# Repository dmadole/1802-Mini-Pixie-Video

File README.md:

# 1802-Mini-Pixie-Video
This is the Pixie video card for the [1802/Mini](https://github.com/dmadole/1802-Mini) system. It supports the following features:

* Software compatible with CDP1861 Pixie chip
* Composite video output with improved sync signalling
* Uses WAIT to syncronize to processor rather than losing sync
* Processor runs at full speed when video is diabled
* Optionally runs processor at full speed outside display area
* Outputs video levels for 75-ohm or high-impedance inputs
* Requires no programmable components, only common 4000-series CMOS
* Supports group I/O port expansion
* Fixed port address of 1 compatible with VIP and Studio II
* Jumper-selected display field polling bit on EF1-EF4

Gerber files for the PCBs and PDF schematics can be found in [Releases](https://github.com/dmadole/1802-Mini-Pixie-Video/releases).

BOMS and any applicable errata or other notes can be found in [notes](https://github.com/dmadole/1802-Mini-Pixie-Video/tree/main/notes).

For availability of kits and bare PCBs please see http://madole.net/1802/mini/kits

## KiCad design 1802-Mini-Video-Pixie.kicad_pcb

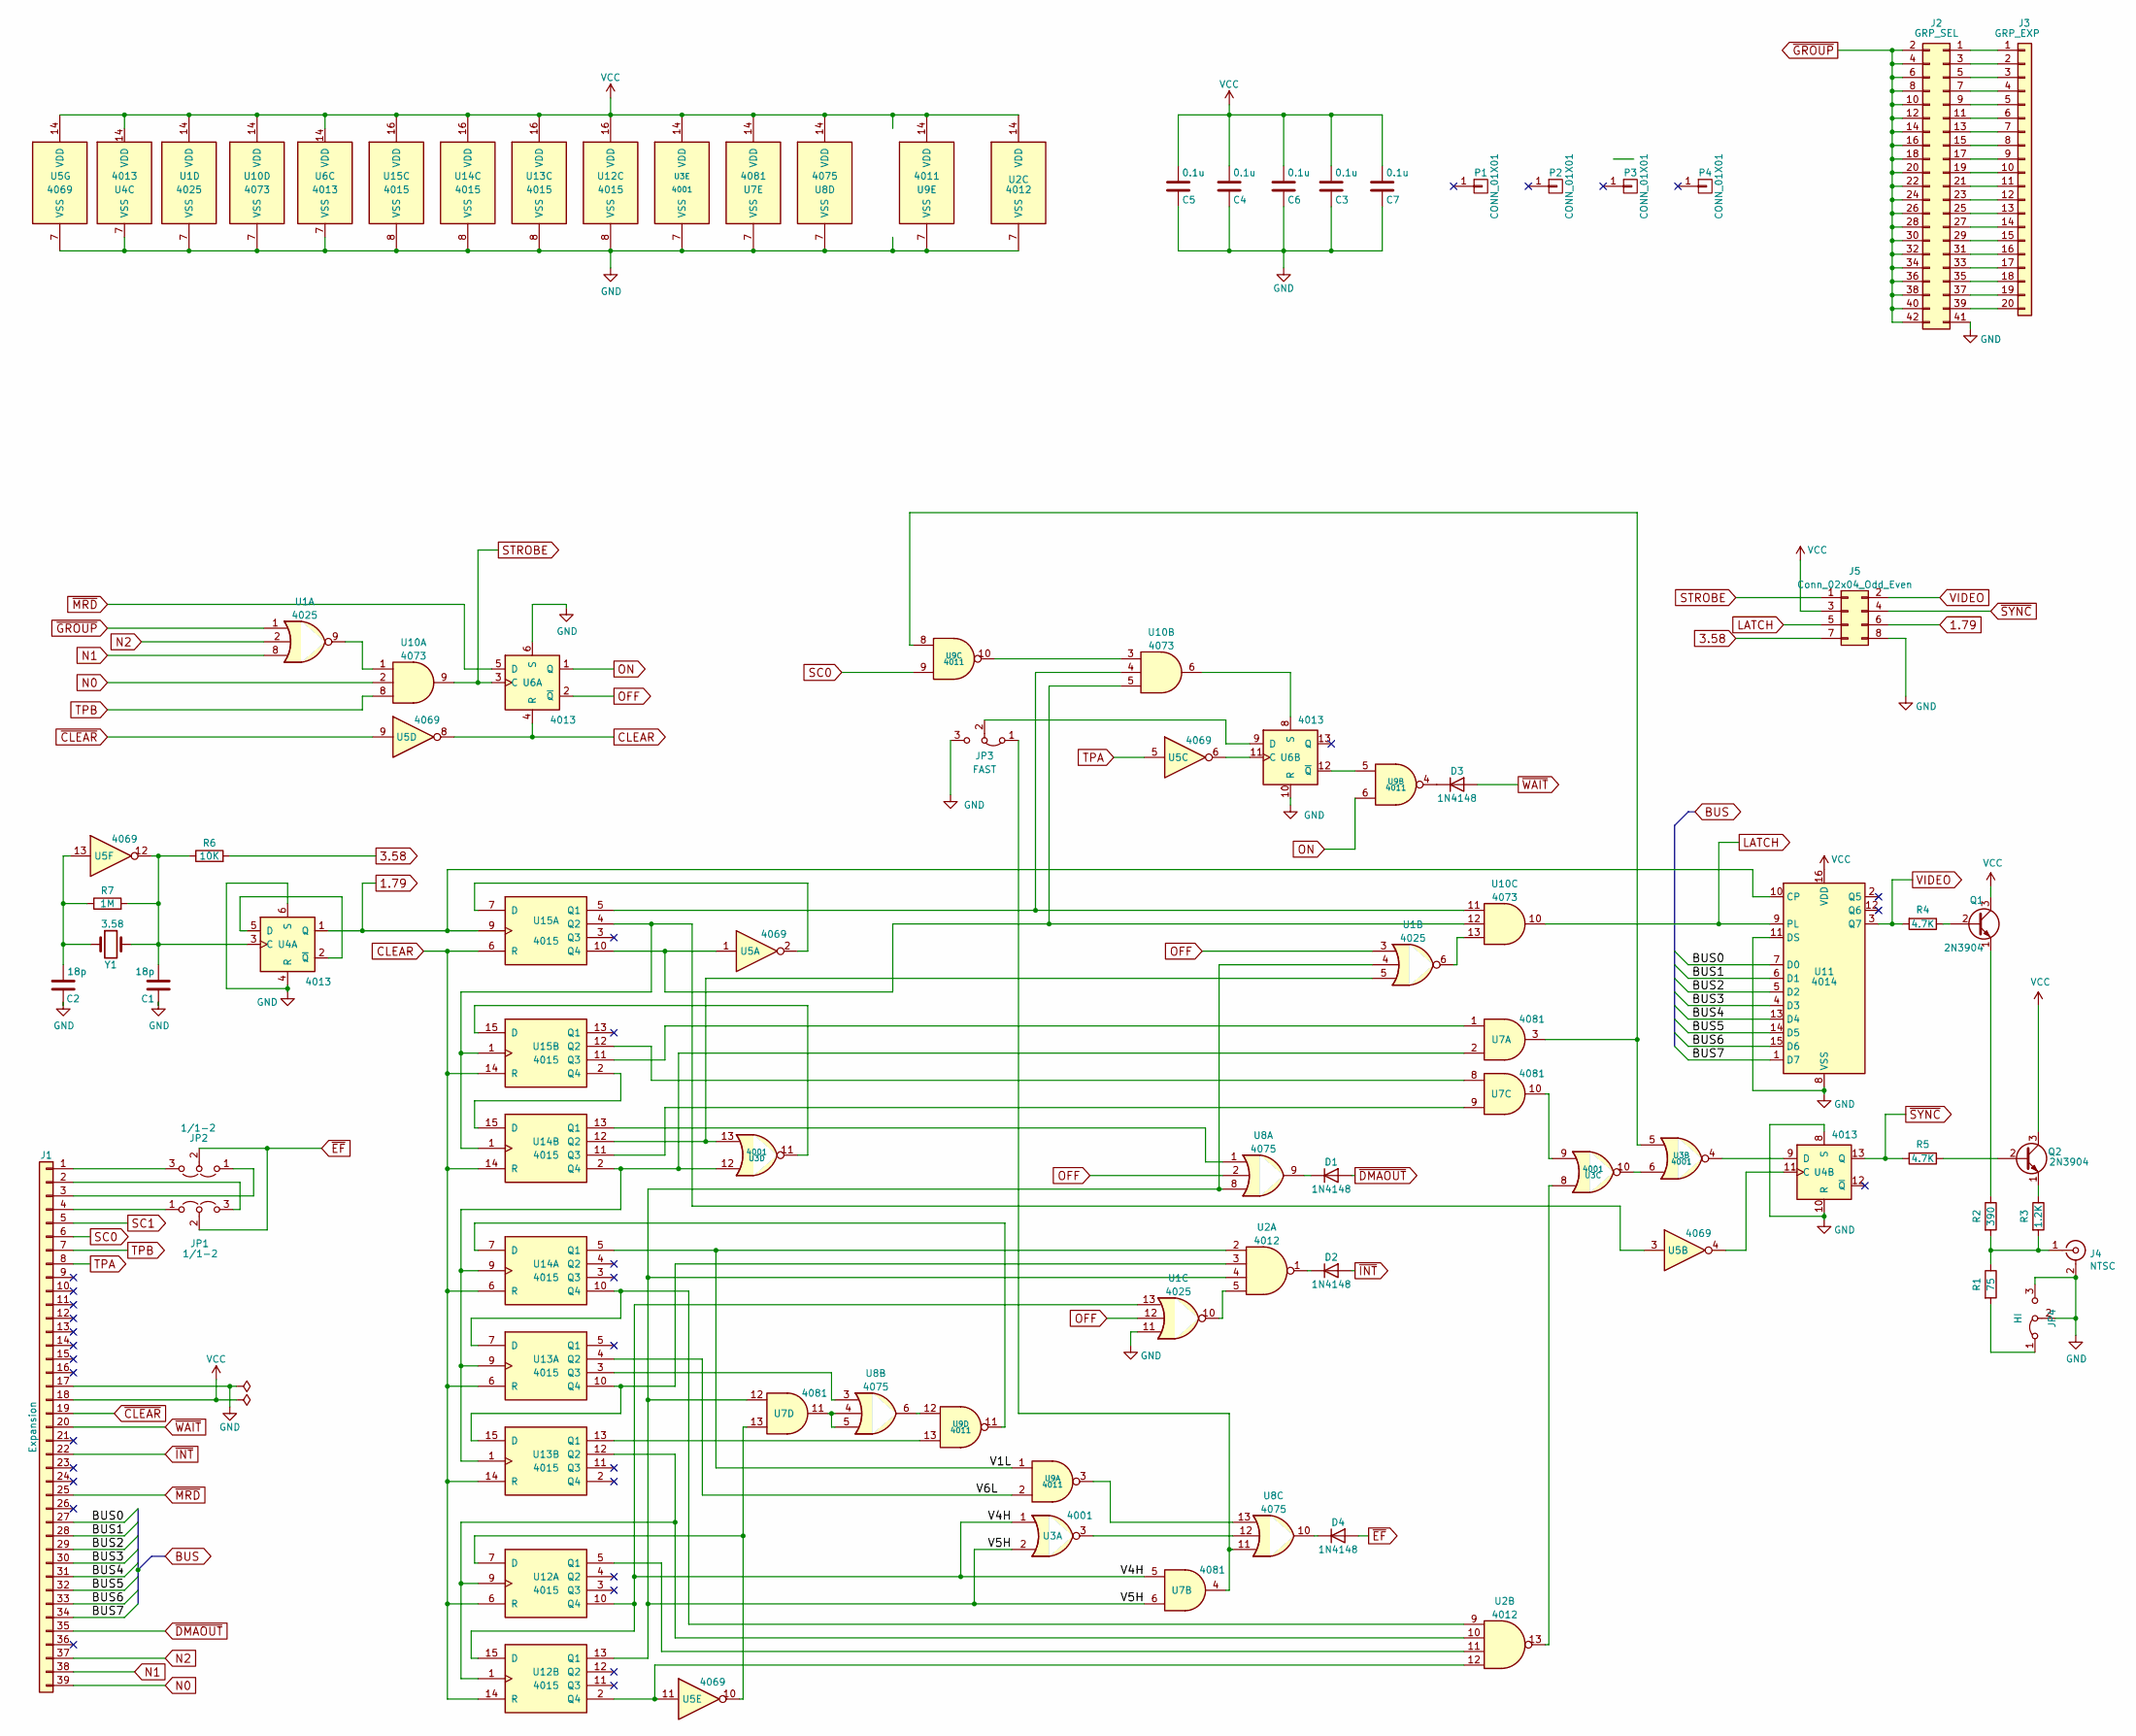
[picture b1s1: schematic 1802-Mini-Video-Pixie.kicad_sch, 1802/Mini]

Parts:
C1, C2: 18p; C_Disc_D4.3mm_W1.9mm_P5.00mm
C3, C4, C5, C6, C7: 0.1u; C_Disc_D4.3mm_W1.9mm_P5.00mm
D1, D2, D3, D4: 1N4148; D_DO-34_SOD68_P7.62mm_Horizontal
J1: Expansion; PinHeader_1x39_P2.54mm_Vertical
J2: GRP_SEL; PinHeader_2x21_P2.54mm_Vertical
J3: GRP_EXP; PinHeader_1x20_P2.54mm_Vertical
J4: NTSC; CUI RCJ-04X
J5: Conn_02x04_Odd_Even; PinHeader_2x04_P2.54mm_Horizontal
JP1, JP2: 1/1-2; PinHeader_1x03_P2.54mm_Vertical
JP3: FAST; PinHeader_1x03_P2.54mm_Vertical
JP4: HI; PinHeader_1x03_P2.54mm_Vertical
P1, P2, P3, P4: CONN_01X01; 1pin
Q1, Q2: 2N3904; TO-92_Inline
R1: 75; R_Axial_DIN0207_L6.3mm_D2.5mm_P10.16mm_Horizontal
R2: 390; R_Axial_DIN0207_L6.3mm_D2.5mm_P10.16mm_Horizontal
R3: 1.2K; R_Axial_DIN0207_L6.3mm_D2.5mm_P10.16mm_Horizontal
R4, R5: 4.7K; R_Axial_DIN0207_L6.3mm_D2.5mm_P10.16mm_Horizontal
R6: 10K; R_Axial_DIN0207_L6.3mm_D2.5mm_P10.16mm_Horizontal
R7: 1M; R_Axial_DIN0207_L6.3mm_D2.5mm_P10.16mm_Horizontal
U1: 4025; DIP-14_W7.62mm_Socket
U2: 4012; DIP-14_W7.62mm_Socket
U3: 4001; DIP-14_W7.62mm_Socket
U4, U6: 4013; DIP-14_W7.62mm_Socket
U5: 4069; DIP-14_W7.62mm_Socket
U7: 4081; DIP-14_W7.62mm_Socket
U8: 4075; DIP-14_W7.62mm_Socket
U9: 4011; DIP-14_W7.62mm_Socket
U10: 4073; DIP-14_W7.62mm_Socket
U11: 4014; DIP-16_W7.62mm_Socket
U12, U13, U14, U15: 4015; DIP-16_W7.62mm_Socket
Y1: 3.58; Crystal_HC49-U_Vertical

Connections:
1.79: J5.6, U4.1 (Q), U11.10 (CP), U15.9
3.58: J5.7, R6.2
/BUS0: J1.27, U11.7 (D0)
/BUS1: J1.28, U11.6 (D1)
/BUS2: J1.29, U11.5 (D2)
/BUS3: J1.30, U11.4 (D3)
/BUS4: J1.31, U11.13 (D4)
/BUS5: J1.32, U11.14 (D5)
/BUS6: J1.33, U11.15 (D6)
/BUS7: J1.34, U11.1 (D7)
/V1L: U2.2, U9.1, U14.5 (Q1)
/V4H: U1.13, U3.1, U7.5, U12.10 (Q4), U12.15 (D)
/V5H: U1.4, U2.4, U3.2, U7.6, U7.12, U8.8, U12.13 (Q1)
/V6L: U9.2, U13.4 (Q2)
CLEAR: U5.8, U6.4 (R), U12.6 (R), U12.14 (R), U13.6 (R), U13.14 (R), U14.6 (R), U14.14 (R), U15.6 (R), U15.14 (R)
GND: C1.1, C2.1, C3.1, C4.1, C5.1, C6.1, C7.1, J1.17, J2.41, J4.2 (Ext), J5.8, JP3.3 (B), JP4.2 (C), JP4.3 (B), U1.7 (VSS), U1.11, U2.7 (VSS), U3.7 (VSS), U4.4 (R), U4.6 (S), U4.7 (VSS), U4.8 (S), U4.10 (R), U5.7 (VSS), U6.6 (S), U6.7 (VSS), U6.10 (R), U7.7 (VSS), U8.7 (VSS), U9.7 (VSS), U10.7 (VSS), U11.8 (VSS), U11.11 (DS), U12.8 (VSS), U13.8 (VSS), U14.8 (VSS), U15.8 (VSS)
LATCH: J5.5, U10.10, U11.9 (PL)
N0: J1.39, U10.2
N1: J1.38, U1.8
N2: J1.37, U1.2
unnamed: C1.2, R6.1, R7.2, U4.3 (C), U5.12, Y1.2
unnamed: C2.2, R7.1, U5.13, Y1.1
unnamed: D1.1 (K), U8.9
unnamed: D2.1 (K), U2.1
unnamed: D3.1 (K), U9.4
unnamed: D4.1 (K), U8.10
unnamed: J1.1, JP1.3 (B)
unnamed: J1.2, JP2.3 (B)
unnamed: J1.3, JP1.1 (A)
unnamed: J1.4, JP2.1 (A)
unnamed: J2.1, J3.1
unnamed: J2.3, J3.2
unnamed: J2.5, J3.3
unnamed: J2.7, J3.4
unnamed: J2.9, J3.5
unnamed: J2.11, J3.6
unnamed: J2.13, J3.7
unnamed: J2.15, J3.8
unnamed: J2.17, J3.9
unnamed: J2.19, J3.10
unnamed: J2.21, J3.11
unnamed: J2.23, J3.12
unnamed: J2.25, J3.13
unnamed: J2.27, J3.14
unnamed: J2.29, J3.15
unnamed: J2.31, J3.16
unnamed: J2.33, J3.17
unnamed: J2.35, J3.18
unnamed: J2.37, J3.19
unnamed: J2.39, J3.20
unnamed: J4.1 (In), R1.1, R2.2, R3.2
unnamed: JP3.1 (A), U7.4, U8.11
unnamed: JP3.2 (C), U6.9 (D)
unnamed: JP4.1 (A), R1.2
unnamed: Q1.1 (E), R2.1
unnamed: Q1.2 (B), R4.1
unnamed: Q2.1 (E), R3.1
unnamed: Q2.2 (B), R5.1
unnamed: U1.5, U3.13, U14.12 (Q2)
unnamed: U1.6, U10.13
unnamed: U1.9, U10.1
unnamed: U1.10, U2.5
unnamed: U2.13, U3.8
unnamed: U3.3, U8.12
unnamed: U3.4, U4.9 (D)
unnamed: U3.5, U7.3, U9.8
unnamed: U3.9, U7.10
unnamed: U3.6, U3.10
unnamed: U4.2 (~Q), U4.5 (D)
unnamed: U4.11 (C), U5.4
unnamed: U5.6, U6.11 (C)
unnamed: U6.12 (~Q), U9.5
unnamed: U7.11, U8.4, U8.5
unnamed: U8.6, U9.12
unnamed: U8.13, U9.3
unnamed: U9.10, U10.3
unnamed: U6.8 (S), U10.6
unnamed: U10.4, U10.11, U15.5 (Q1)
unnamed: U5.1, U10.5, U10.12, U15.10 (Q4)
unnamed: U2.12, U5.11, U12.2 (Q4)
unnamed: U2.11, U12.5 (Q1)
unnamed: U5.10, U7.13, U12.7 (D)
unnamed: U3.12, U7.2, U13.1, U13.9, U14.2 (Q4), U14.9
unnamed: U8.3, U13.3 (Q3)
unnamed: U2.9, U13.7 (D), U14.10 (Q4)
unnamed: U2.3, U13.10 (Q4), U13.15 (D)
unnamed: U2.10, U12.1, U12.9, U13.12 (Q2)
unnamed: U9.13, U13.13 (Q1)
unnamed: U5.3, U14.1, U15.1, U15.4 (Q2)
unnamed: U9.11, U14.7 (D)
unnamed: U7.9, U14.11 (Q3)
unnamed: U8.1, U14.13 (Q1)
unnamed: U14.15 (D), U15.2 (Q4)
unnamed: U5.2, U15.7 (D)
unnamed: U7.1, U15.11 (Q3)
unnamed: U7.8, U15.12 (Q2)
unnamed: U3.11, U15.15 (D)
OFF: U1.3, U1.12, U6.2 (~Q), U8.2
ON: U6.1 (Q), U9.6
SC0: J1.6, U9.9
SC1: J1.5
STROBE: J5.1, U6.3 (C), U10.9
TPA: J1.8, U5.5
TPB: J1.7, U10.8
VCC: C3.2, C4.2, C5.2, C6.2, C7.2, J1.18, J5.3, Q1.3 (C), Q2.3 (C), U1.14 (VDD), U2.14 (VDD), U3.14 (VDD), U4.14 (VDD), U5.14 (VDD), U6.14 (VDD), U7.14 (VDD), U8.14 (VDD), U9.14 (VDD), U10.14 (VDD), U11.16 (VDD), U12.16 (VDD), U13.16 (VDD), U14.16 (VDD), U15.16 (VDD)
VIDEO: J5.2, R4.2, U11.3 (Q7)
~CLEAR: J1.19, U5.9
~DMAOUT: D1.2 (A), J1.35
~EF: D4.2 (A), JP1.2 (C), JP2.2 (C)
~GROUP: J2.2, J2.4, J2.6, J2.8, J2.10, J2.12, J2.14, J2.16, J2.18, J2.20, J2.22, J2.24, J2.26, J2.28, J2.30, J2.32, J2.34, J2.36, J2.38, J2.40, J2.42, U1.1
~INT: D2.2 (A), J1.22
~MRD: J1.25, U6.5 (D)
~SYNC: J5.4, R5.2, U4.13 (Q)
~WAIT: D3.2 (A), J1.20

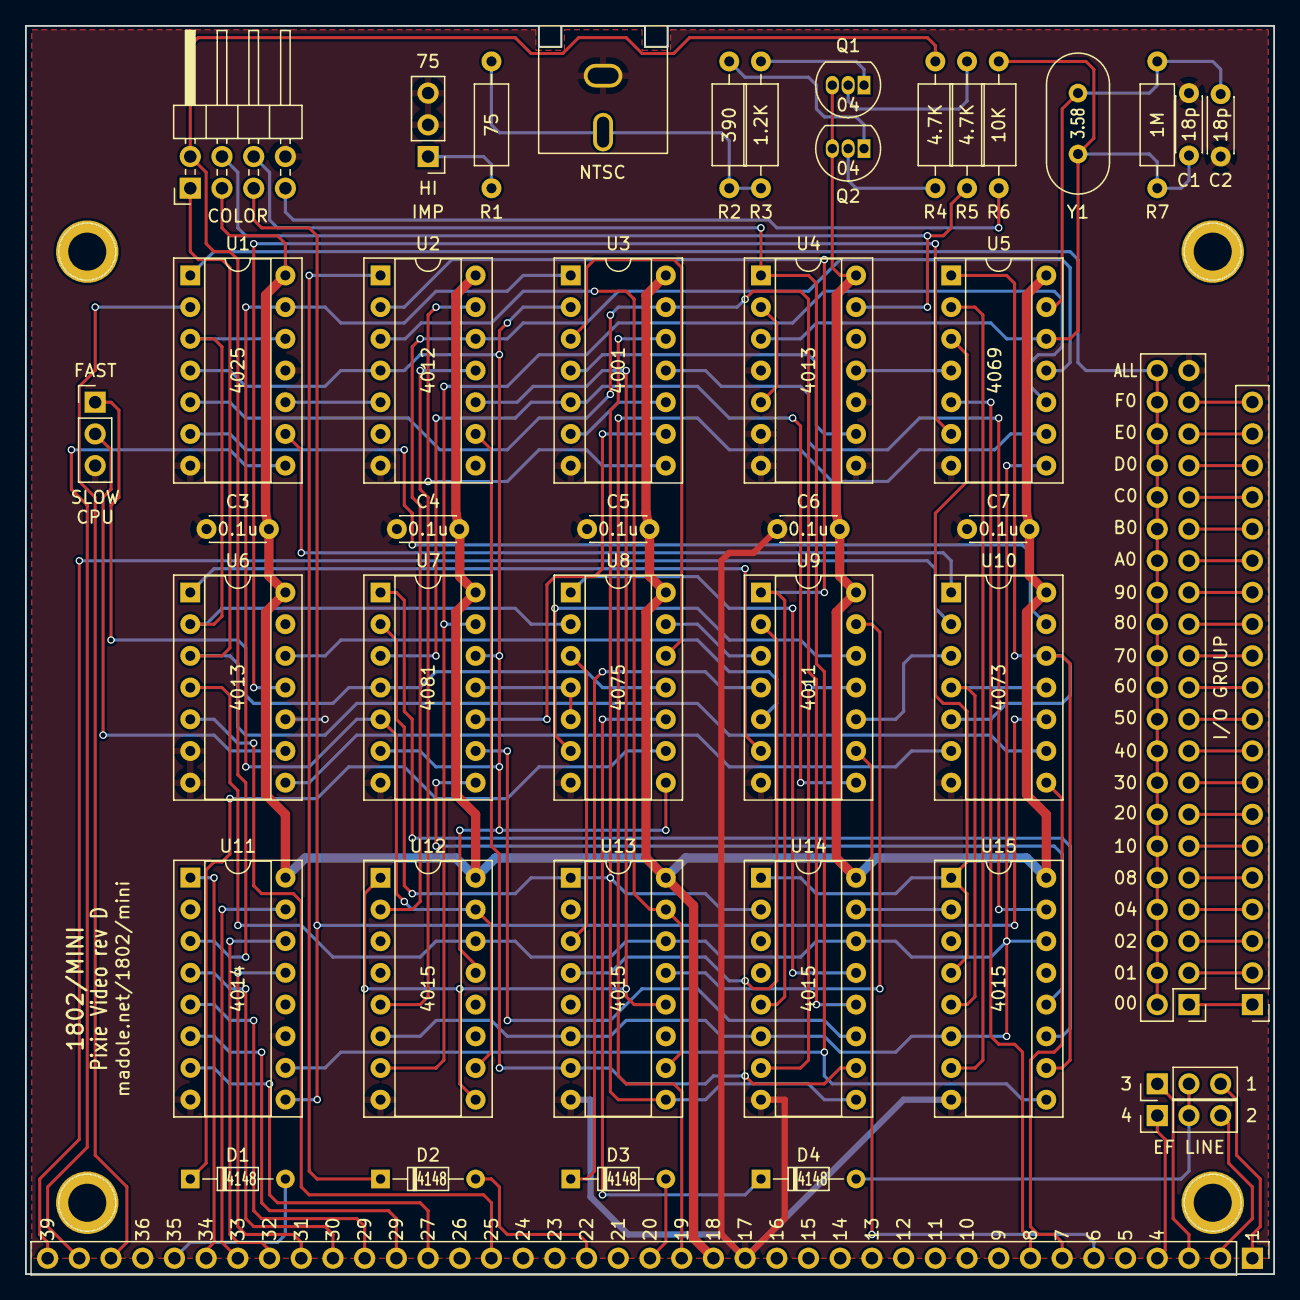
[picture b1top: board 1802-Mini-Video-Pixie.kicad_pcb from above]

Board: 2 copper layers, 100.0 x 100.0 mm, 49 parts (0 on the bottom side), 113 nets.

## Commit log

2024-01-31 Fix image link
2024-01-31 One more try on image
2024-02-05 Fix date
